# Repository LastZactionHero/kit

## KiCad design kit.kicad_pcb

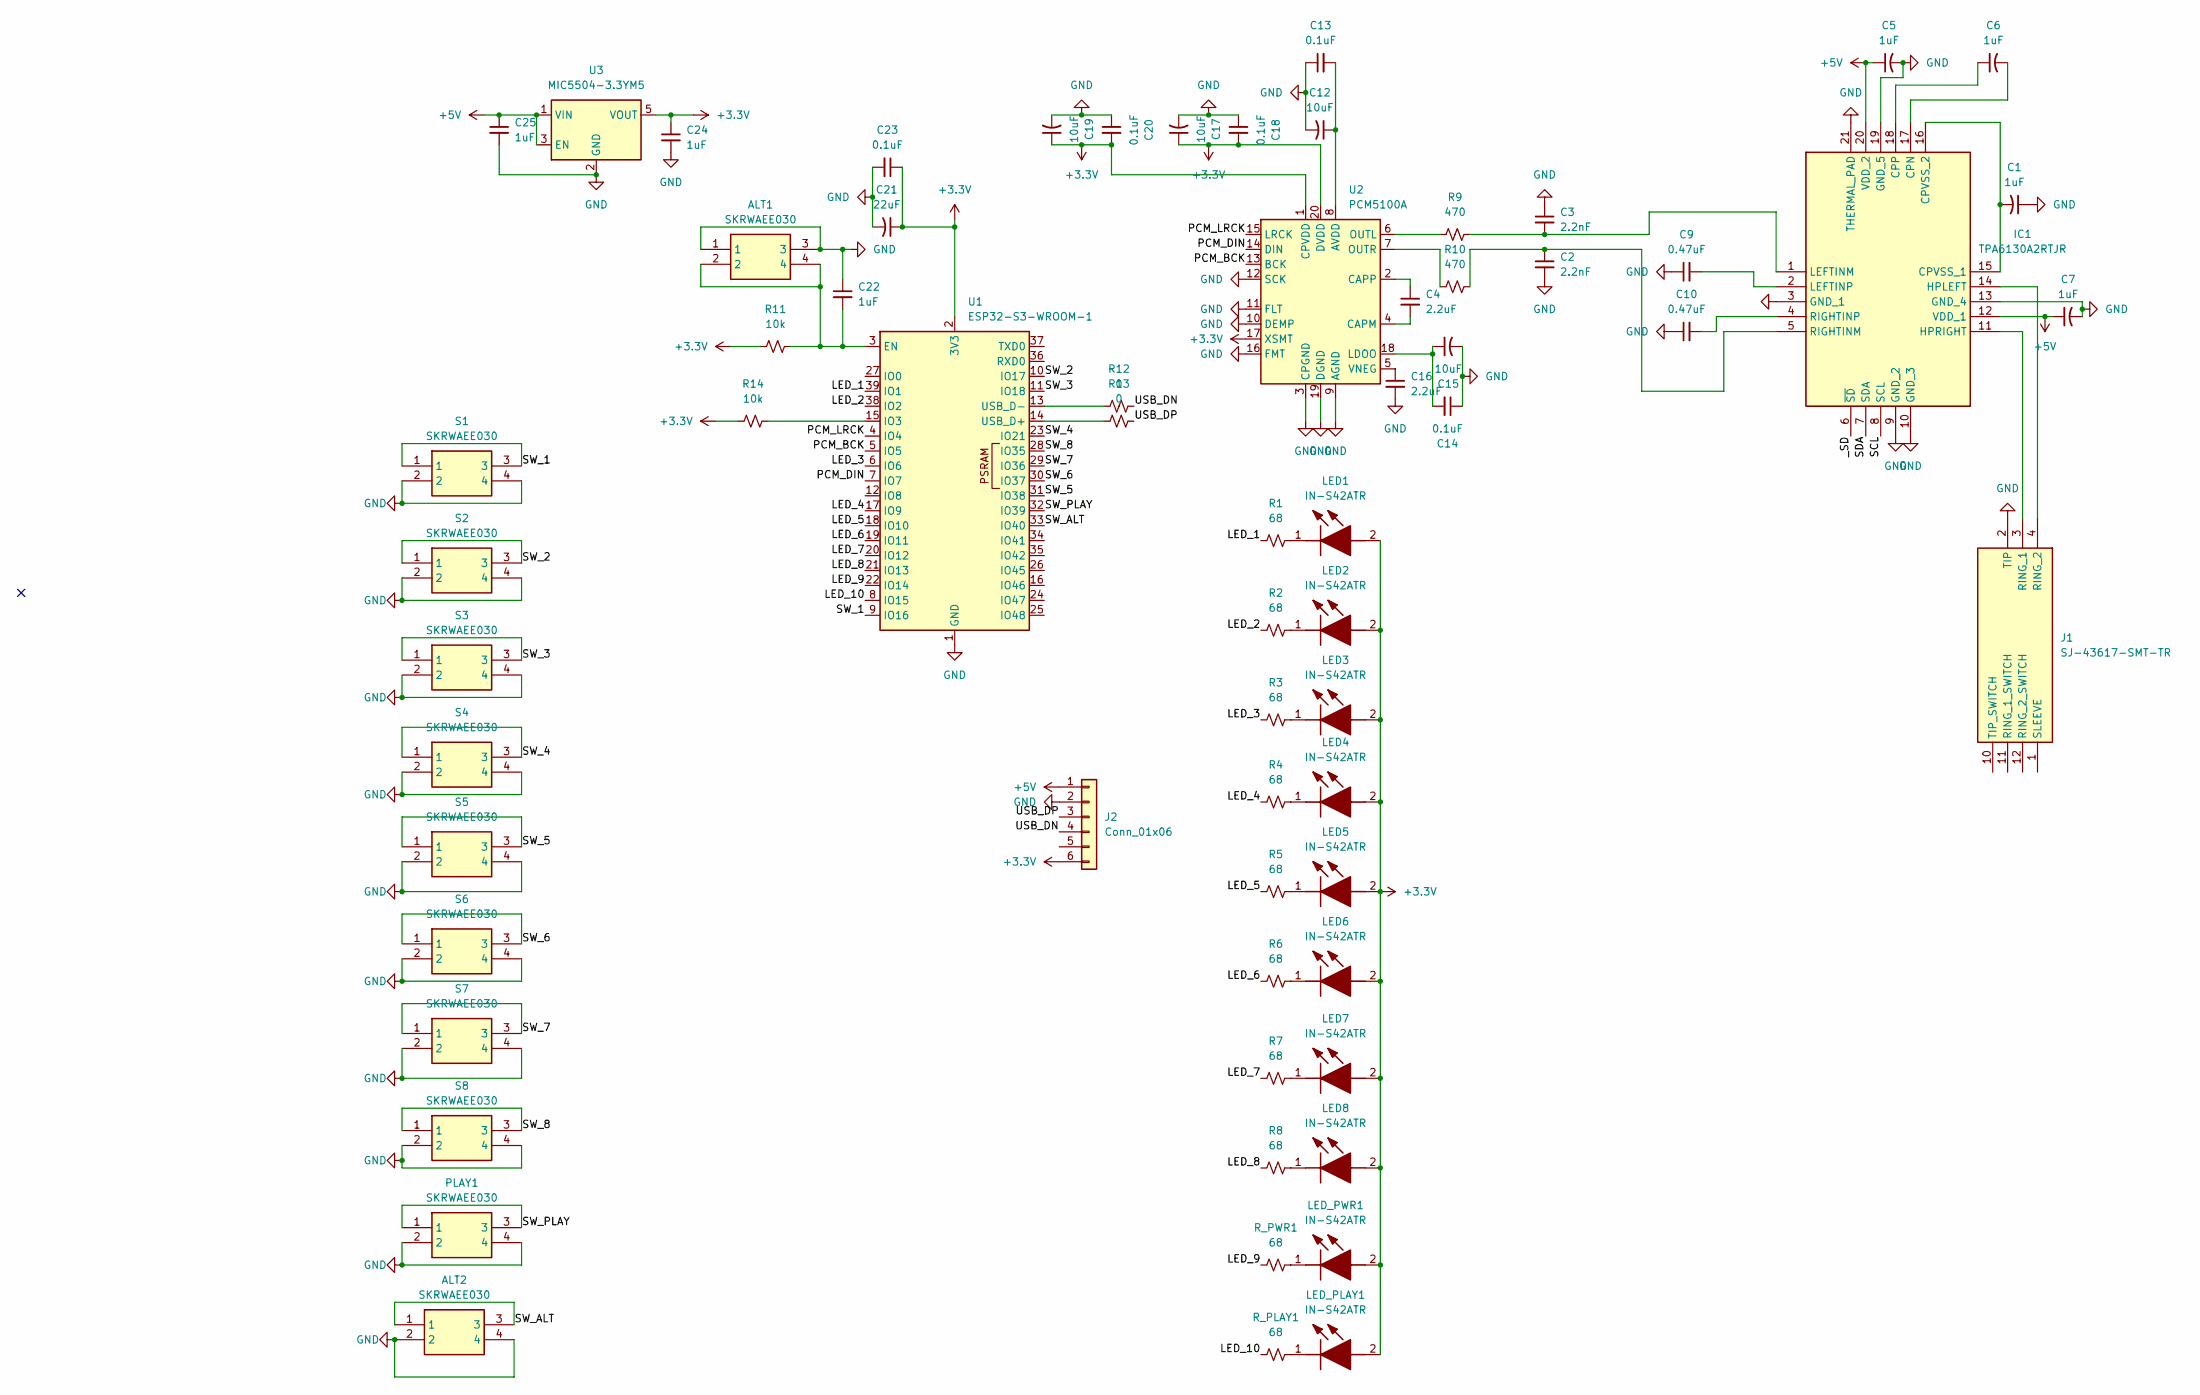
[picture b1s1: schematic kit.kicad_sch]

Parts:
ALT1, ALT2: SKRWAEE030; Mouser Part Number 688-SKRWAEE030
C1, C5, C6, C7, C22, C24, C25: 1uF; C_01005_0402Metric
C2, C3: 2.2nF; C_01005_0402Metric
C4, C16: 2.2uF; C_01005_0402Metric
C9, C10: 0.47uF; C_01005_0402Metric
C12, C15, C17, C19: 10uF; C_01005_0402Metric
C13, C14, C18, C20, C23: 0.1uF; C_01005_0402Metric
C21: 22uF; C_01005_0402Metric
IC1: TPA6130A2RTJR; QFN50P400X400X80-21N-D; Mouser Part Number 595-TPA6130A2RTJR
J1: SJ-43617-SMT-TR; SJ43617SMTTR; Mouser Part Number 490-SJ-43617-SMT-TR
J2: Conn_01x06; PinHeader_1x06_P2.54mm_Vertical
LED1, LED2, LED3, LED4, LED5, LED6, LED7, LED8: IN-S42ATR; LEDC1005X55N; Mouser Part Number 743-IN-S42ATR
LED_PLAY1: IN-S42ATR; LEDC1005X55N; Mouser Part Number 743-IN-S42ATR
LED_PWR1: IN-S42ATR; LEDC1005X55N; Mouser Part Number 743-IN-S42ATR
PLAY1: SKRWAEE030; Mouser Part Number 688-SKRWAEE030
R1, R2, R3, R4, R5, R6, R7, R8: 68; R_01005_0402Metric
R9, R10: 470; R_01005_0402Metric
R11, R14: 10k; R_01005_0402Metric
R12, R13: 0; R_01005_0402Metric
R_PLAY1: 68; R_01005_0402Metric
R_PWR1: 68; R_01005_0402Metric
S1, S2, S3, S4, S5, S6, S7, S8: SKRWAEE030; Mouser Part Number 688-SKRWAEE030
U1: ESP32-S3-WROOM-1
U2: PCM5100A; TSSOP-20_4.4x6.5mm_P0.65mm
U3: MIC5504-3.3YM5; SOT-23-5

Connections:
+3.3V: C17.1, C18.2, C19.1, C20.2, C21.1, C23.1, C24.1, J2.6, LED1.2 (A), LED2.2 (A), LED3.2 (A), LED4.2 (A), LED5.2 (A), LED6.2 (A), LED7.2 (A), LED8.2 (A), LED_PLAY1.2 (A), LED_PWR1.2 (A), R11.1, R14.1, U1.2 (3V3), U2.1 (CPVDD), U2.17 (XSMT), U2.20 (DVDD), U3.5 (VOUT)
+5V: C5.1, C7.1, C25.1, IC1.12 (VDD_1), IC1.20 (VDD_2), J2.1, U3.1 (VIN), U3.3 (EN)
/LED_1: R1.1, U1.39 (IO1)
/LED_2: R2.1, U1.38 (IO2)
/LED_3: R3.1, U1.6 (IO6)
/LED_4: R4.1, U1.17 (IO9)
/LED_5: R5.1, U1.18 (IO10)
/LED_6: R6.1, U1.19 (IO11)
/LED_7: R7.1, U1.20 (IO12)
/LED_8: R8.1, U1.21 (IO13)
/LED_9: R_PWR1.1, U1.22 (IO14)
/LED_10: R_PLAY1.1, U1.8 (IO15)
/PCM_BCK: U1.5 (IO5), U2.13 (BCK)
/PCM_DIN: U1.7 (IO7), U2.14 (DIN)
/PCM_LRCK: U1.4 (IO4), U2.15 (LRCK)
/SCL: IC1.8 (SCL)
/SDA: IC1.7 (SDA)
/SW_1: S1.1, S1.3, U1.9 (IO16)
/SW_2: S2.1, S2.3, U1.10 (IO17)
/SW_3: S3.1, S3.3, U1.11 (IO18)
/SW_4: S4.1, S4.3, U1.23 (IO21)
/SW_5: S5.1, S5.3, U1.31 (IO38)
/SW_6: S6.1, S6.3, U1.30 (IO37)
/SW_7: S7.1, S7.3, U1.29 (IO36)
/SW_8: S8.1, S8.3, U1.28 (IO35)
/SW_ALT: ALT2.1, ALT2.3, U1.33 (IO40); also elsewhere on the board
/SW_PLAY: PLAY1.1, PLAY1.3, U1.32 (IO39); also elsewhere on the board
/USB_DN: J2.4, R12.2
/USB_DP: J2.3, R13.2
/_SD: IC1.6 (~SD)
GND: ALT1.1, ALT1.3, ALT2.2, ALT2.4, C1.1, C2.2, C3.1, C5.2, C7.2, C9.1, C10.1, C12.2, C13.1, C14.1, C15.2, C16.2, C17.2, C18.1, C19.2, C20.1, C21.2, C22.1, C23.2, C24.2, C25.2, IC1.3 (GND_1), IC1.9 (GND_2), IC1.10 (GND_3), IC1.13 (GND_4), IC1.19 (GND_5), IC1.21 (THERMAL_PAD), J1.2 (TIP), J2.2, PLAY1.2, PLAY1.4, S1.2, S1.4, S2.2, S2.4, S3.2, S3.4, S4.2, S4.4, S5.2, S5.4, S6.2, S6.4, S7.2, S7.4, S8.2, S8.4, U1.1 (GND), U1.40 (GND), U1.41 (GND), U2.3 (CPGND), U2.9 (AGND), U2.10 (DEMP), U2.11 (FLT), U2.12 (SCK), U2.16 (FMT), U2.19 (DGND), U3.2 (GND); also elsewhere on the board
unnamed: C6.2, IC1.17 (CPN)
unnamed: C6.1, IC1.18 (CPP)
unnamed: C1.2, IC1.15 (CPVSS_1), IC1.16 (CPVSS_2)
unnamed: IC1.14 (HPLEFT), J1.4 (RING_2)
unnamed: IC1.11 (HPRIGHT), J1.3 (RING_1)
unnamed: C3.2, IC1.1 (LEFTINM), R9.2
unnamed: C9.2, IC1.2 (LEFTINP)
unnamed: C2.1, IC1.5 (RIGHTINM), R10.2
unnamed: C10.2, IC1.4 (RIGHTINP)
unnamed: LED1.1 (K), R1.2
unnamed: LED2.1 (K), R2.2
unnamed: LED3.1 (K), R3.2
unnamed: LED4.1 (K), R4.2
unnamed: LED5.1 (K), R5.2
unnamed: LED6.1 (K), R6.2
unnamed: LED7.1 (K), R7.2
unnamed: LED8.1 (K), R8.2
unnamed: LED_PLAY1.1 (K), R_PLAY1.2
unnamed: LED_PWR1.1 (K), R_PWR1.2
unnamed 50: ALT1.2, ALT1.4, C22.2, R11.2, U1.3 (EN); also elsewhere on the board
unnamed: R14.2, U1.15 (IO3)
unnamed: R13.1, U1.14 (USB_D+)
unnamed: R12.1, U1.13 (USB_D-)
unnamed: C12.1, C13.2, U2.8 (AVDD)
unnamed: C4.2, U2.4 (CAPM)
unnamed: C4.1, U2.2 (CAPP)
unnamed: C14.2, C15.1, U2.18 (LDOO)
unnamed: R9.1, U2.6 (OUTL)
unnamed: R10.1, U2.7 (OUTR)
unnamed: C16.1, U2.5 (VNEG)

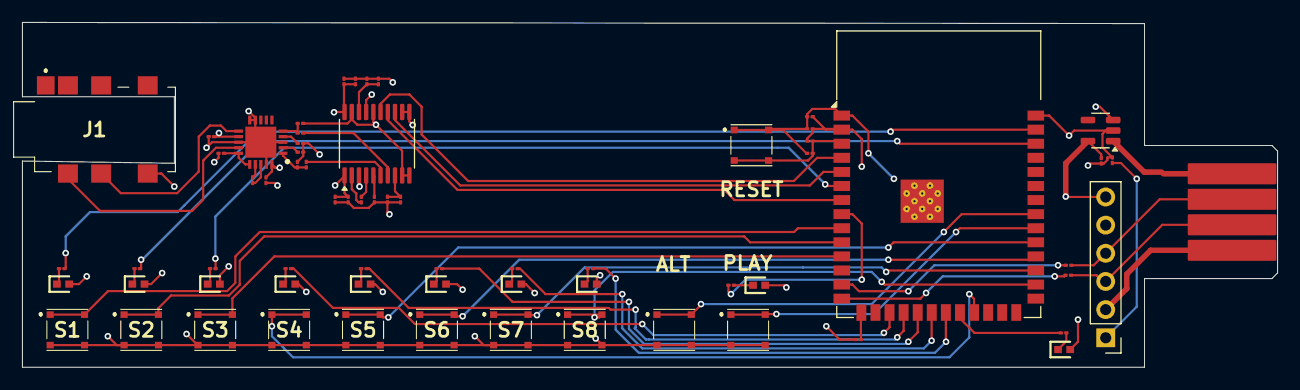
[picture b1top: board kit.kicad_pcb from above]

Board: 4 copper layers, 113.2 x 31.1 mm, 66 parts (0 on the bottom side), 58 nets.

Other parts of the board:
ALT: SKRWAEE030
PLAY: SKRWAEE030
RESET: SKRWAEE030

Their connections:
/SW_ALT: ALT.1, ALT.3; also elsewhere on the board
/SW_PLAY: PLAY.1, PLAY.3; also elsewhere on the board
GND: ALT.2, ALT.4, PLAY.2, PLAY.4, RESET.1, RESET.3; also elsewhere on the board
unnamed 50: RESET.2, RESET.4; also elsewhere on the board
